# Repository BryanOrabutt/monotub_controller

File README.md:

# monotub_controller
A custom mushroom monotub controller based around ESP32

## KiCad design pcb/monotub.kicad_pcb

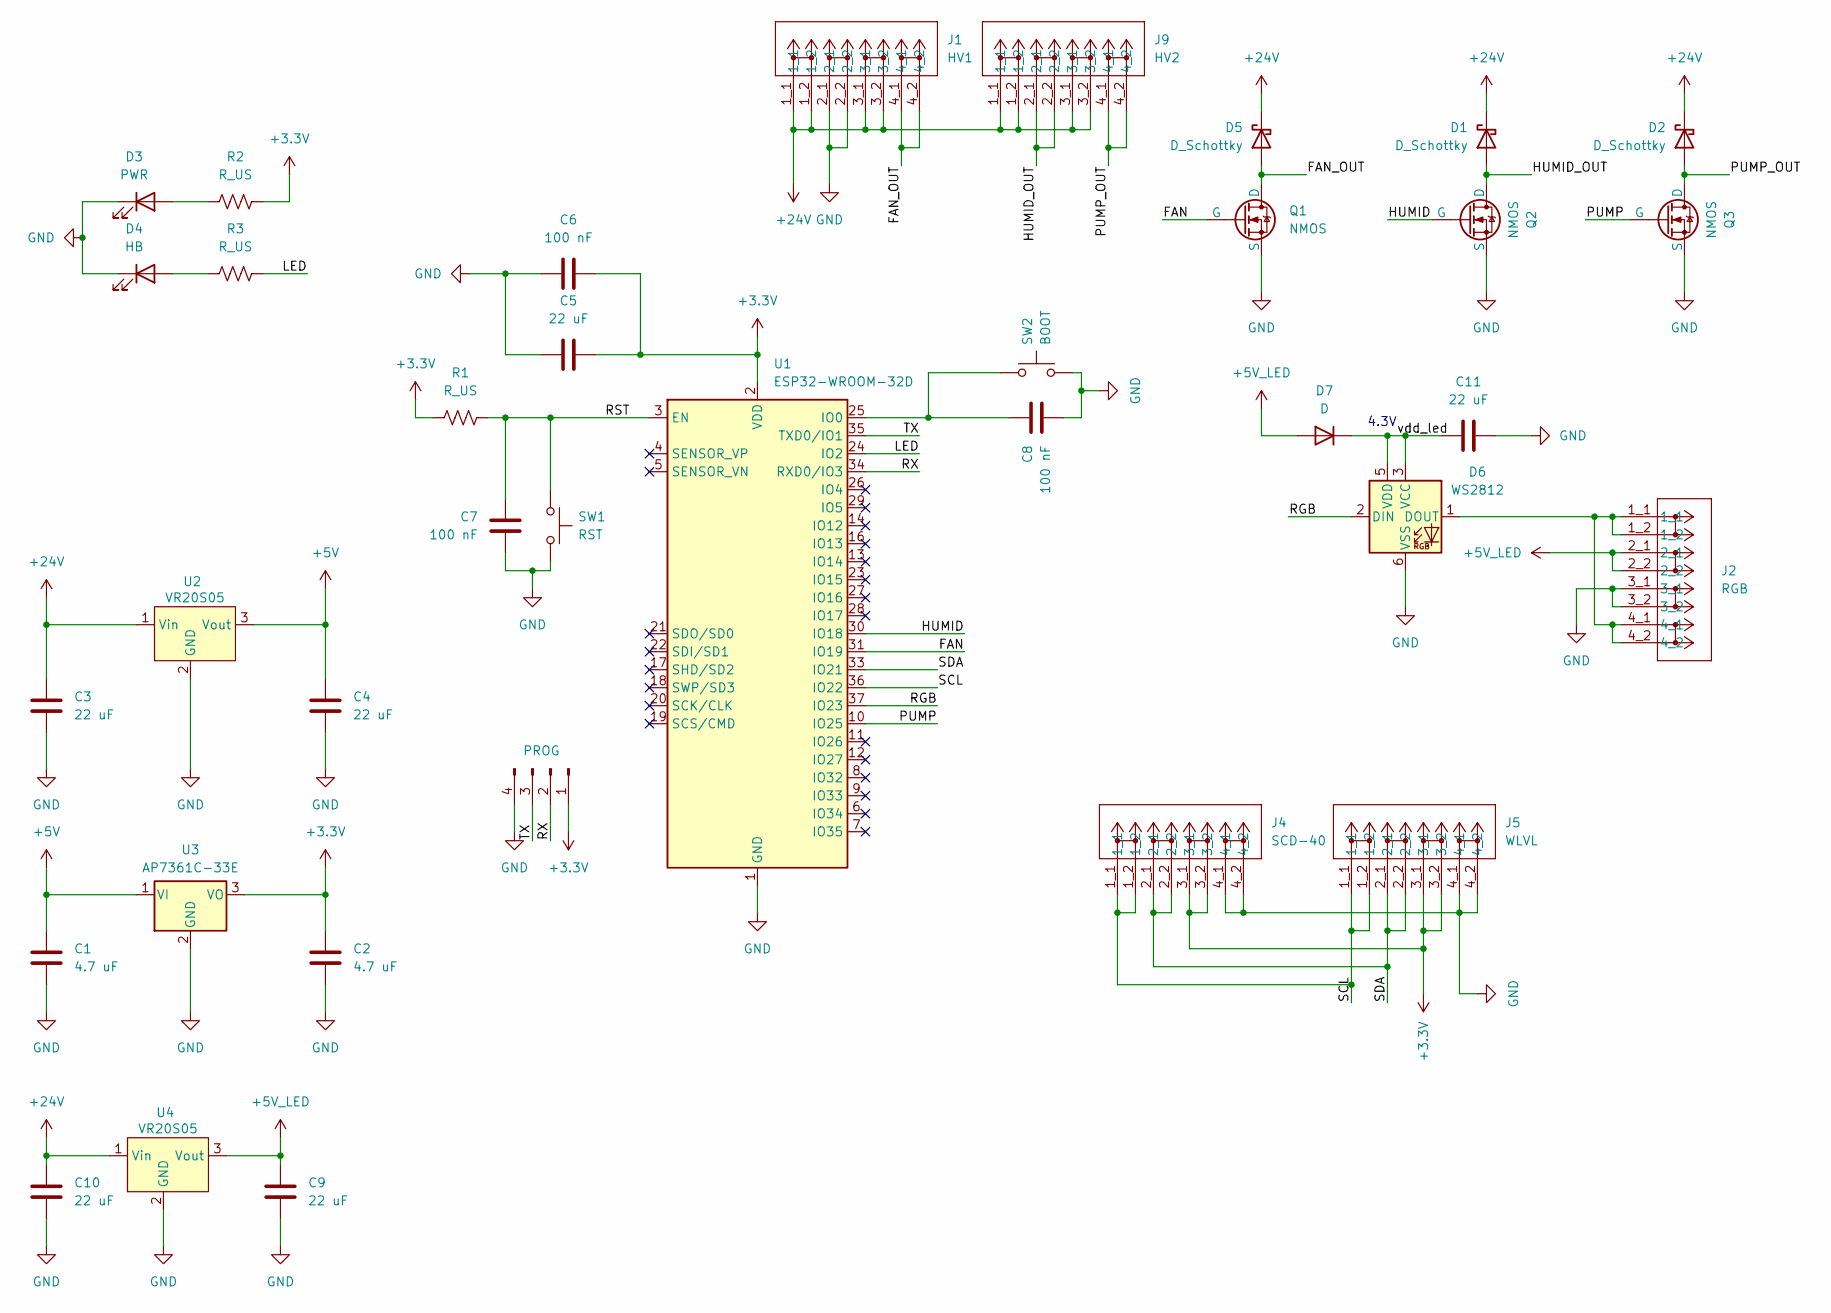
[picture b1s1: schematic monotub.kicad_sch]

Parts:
C1, C2: 4.7 uF; C_0805_2012Metric_Pad1.18x1.45mm_HandSolder
C3, C4, C5, C9, C10, C11: 22 uF; C_0805_2012Metric_Pad1.18x1.45mm_HandSolder
C6, C7, C8: 100 nF; C_0805_2012Metric_Pad1.18x1.45mm_HandSolder
D1, D2, D5: D_Schottky; D_SMA_Handsoldering
D3: PWR; LED_0805_2012Metric_Pad1.15x1.40mm_HandSolder
D4: HB; LED_0805_2012Metric_Pad1.15x1.40mm_HandSolder
D6: WS2812; LED_WS2812_PLCC6_5.0x5.0mm_P1.6mm
D7: D; D_SOD-123
J1: HV1; CONN_2601-1104_WAG
J2: RGB; CONN_2601-1104_WAG
J3: PROG; PinSocket_1x04_P2.54mm_Vertical
J4: SCD-40; CONN_2601-1104_WAG
J5: WLVL; CONN_2601-1104_WAG
J9: HV2; CONN_2601-1104_WAG
Q1, Q2, Q3: NMOS; SOT-23
R1, R2, R3: R_US; R_0805_2012Metric_Pad1.20x1.40mm_HandSolder
SW1: RST; SW_PUSH_6mm
SW2: BOOT; SW_PUSH_6mm
U1: ESP32-WROOM-32D
U2, U4: VR20S05; PinSocket_1x03_P2.54mm_Vertical
U3: AP7361C-33E; SOT-223-3_TabPin2

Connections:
+3.3V: C2.1, C5.1, C6.1, J3.1, J4.3_1, J4.3_2, J5.3_1, J5.3_2, R1.1, R2.2, U1.2 (VDD), U3.3 (VO)
+5V: C1.1, C4.1, U2.3 (Vout), U3.1 (VI)
+5V_LED: C9.1, D7.2 (A), J2.2_1, J2.2_2, U4.3 (Vout)
+24V: C3.1, C10.1, D1.1 (K), D2.1 (K), D5.1 (K), J1.1_1, J1.1_2, J1.3_1, J1.3_2, J9.1_1, J9.1_2, J9.3_1, J9.3_2, U2.1 (Vin), U4.1 (Vin)
/FAN: Q1.2 (G), U1.31 (IO19)
/FAN_OUT: D5.2 (A), J1.4_1, J1.4_2, Q1.1 (D)
/HUMID: Q2.2 (G), U1.30 (IO18)
/HUMID_OUT: D1.2 (A), J9.2_1, J9.2_2, Q2.1 (D)
/LED: R3.2, U1.24 (IO2)
/PUMP: Q3.2 (G), U1.10 (IO25)
/PUMP_OUT: D2.2 (A), J9.4_1, J9.4_2, Q3.1 (D)
/RGB: D6.2 (DIN), U1.37 (IO23)
/RST: C7.1, R1.2, SW1.1, U1.3 (EN); also elsewhere on the board
/RX: J3.2, U1.34 (RXD0/IO3)
/SCL: J4.1_1, J4.1_2, J5.1_1, J5.1_2, U1.36 (IO22)
/SDA: J4.2_1, J4.2_2, J5.2_1, J5.2_2, U1.33 (IO21)
/TX: J3.3, U1.35 (TXD0/IO1)
/vdd_led: C11.1, D6.3 (VCC), D6.5 (VDD), D7.1 (K)
GND: C1.2, C2.2, C3.2, C4.2, C5.2, C6.2, C7.2, C8.2, C9.2, C10.2, C11.2, D3.1 (K), D4.1 (K), D6.6 (VSS), J1.2_1, J1.2_2, J2.3_1, J2.3_2, J3.4, J4.4_1, J4.4_2, J5.4_1, J5.4_2, Q1.3 (S), Q2.3 (S), Q3.3 (S), SW1.2, SW2.2, U1.1 (GND), U1.15 (GND), U1.38 (GND), U1.39 (GND), U2.2 (GND), U3.2 (GND), U4.2 (GND); also elsewhere on the board
unnamed: D3.2 (A), R2.1
unnamed: D4.2 (A), R3.1
unnamed: D6.1 (DOUT), J2.1_1, J2.1_2, J2.4_1, J2.4_2
unnamed 22: C8.1, SW2.1, U1.25 (IO0); also elsewhere on the board

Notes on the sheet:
4.3V

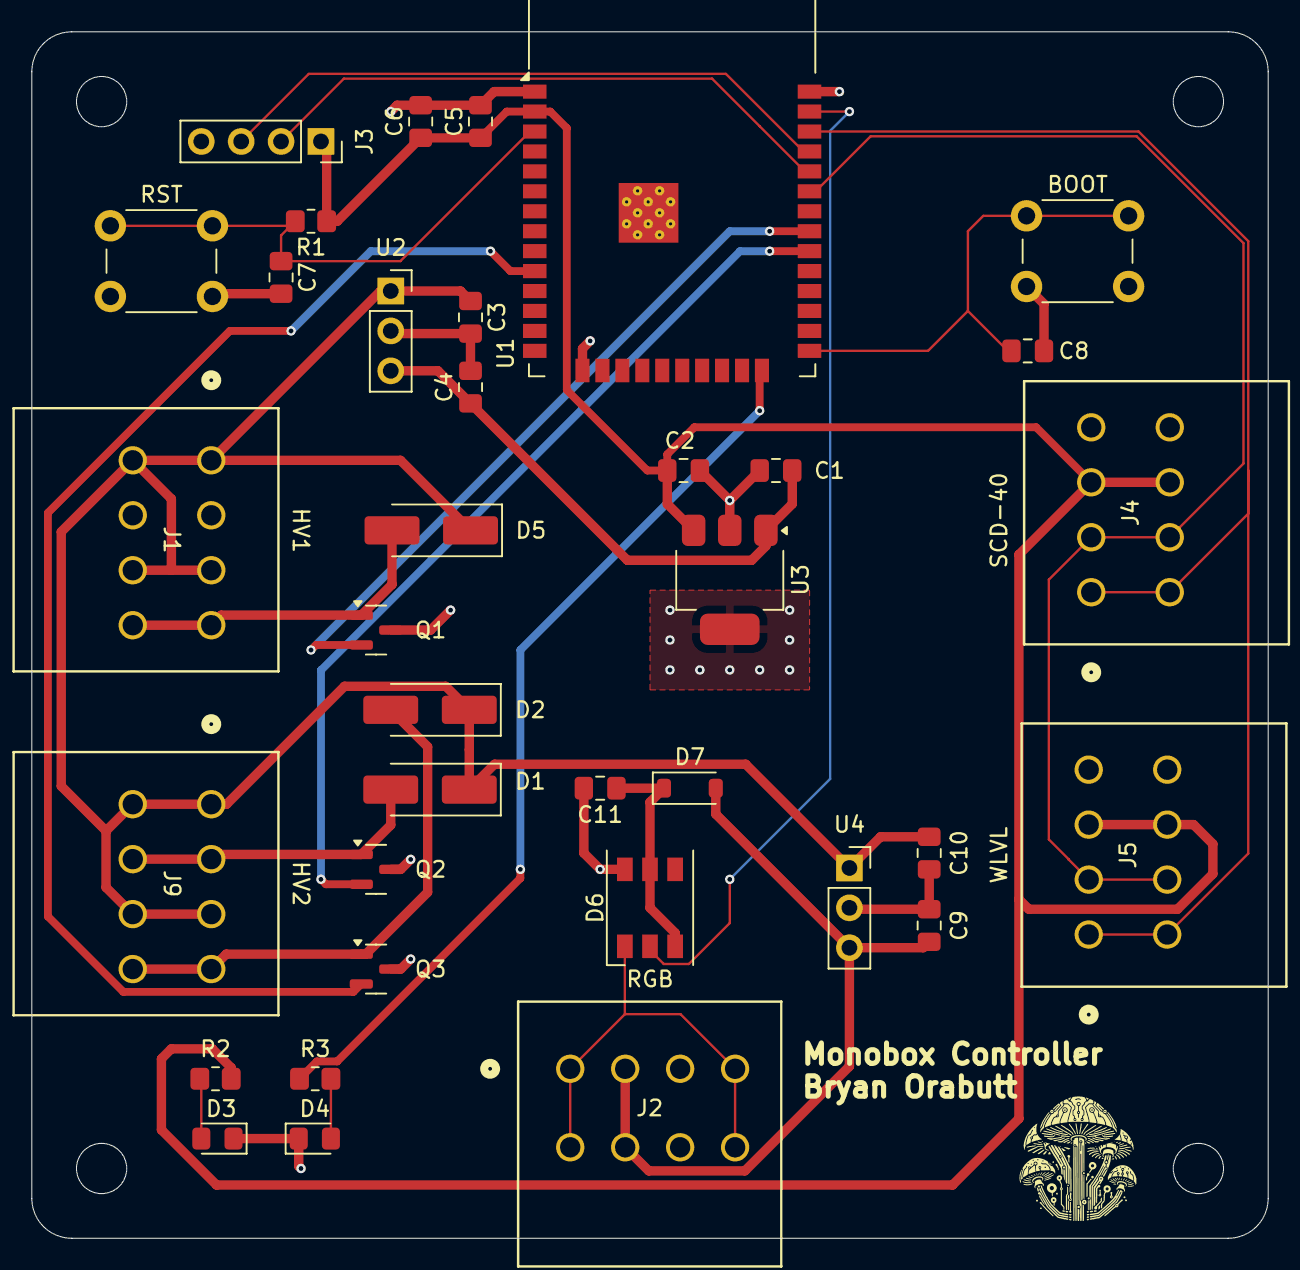
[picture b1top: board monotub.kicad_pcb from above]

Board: 2 copper layers, 78.7 x 76.8 mm, 36 parts (0 on the bottom side), 23 nets.

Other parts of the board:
BOOT: BOOT; SW_PUSH_6mm
RST: RST; SW_PUSH_6mm

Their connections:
/RST: RST.1; also elsewhere on the board
GND: BOOT.2, RST.2; also elsewhere on the board
unnamed 22: BOOT.1; also elsewhere on the board

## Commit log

2024-04-06 Update gitignore for ESP-IDF
2024-04-06 Add project files
2024-04-06 Update gitignore to ignore KConfig files
2024-04-08 Add SCD41 task to measure CO2, Temperature, and Rel humidity.
2024-04-13 Add comments
2024-04-13 Implement xQueue for moving sensor data around.
2024-04-13 Add delay in main task
2024-04-14 Add pin reference and main control loop logic.
2024-04-15 Fix type issue with co2.
2024-05-01 MCPWMs enabled and hysteretic control loop for CO2 working
2024-05-02 Update gitignore for KiCAD
2024-05-02 Add PCB files
2024-05-03 Update schematic with fan, humidifier, and other components.
2024-05-10 Update schematic with regulator for uC and LED seperate
2024-05-10 Update gitignore to exclude .lck files
2024-05-14 Add connectors for water level, pump, and RGB leds
2024-05-14 Add datasheets
2024-05-14 Add datasheets, assign footprints, and start PCB file
2024-05-22 Update board with logo and place all components
2024-05-27 Update PCB routing.
2024-06-13 Finish routing the board
